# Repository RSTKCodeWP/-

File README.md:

# RSTKCodeWP — FPV & drone open-source library

Монорепозиторій з **каталогом**, **дзеркалами** та **legacy-копіями** FPV/drone проєктів з GitHub.

## Швидка навігація

| Документ | Зміст |
|----------|--------|
| **[wiki/Home.md](wiki/Home.md)** | Виставкова вікі: ідея, для чого, для кого, функція, як, що треба, інструкція |
| **[MAP.md](MAP.md)** | Карта всіх тек монорепо — дерево, org-бібліотеки, статус mirror |
| **[REPOS.md](REPOS.md)** | Повний список усіх проєктів: опис · тека · дата · розмір |
| **[docs/STRUCTURE.md](docs/STRUCTURE.md)** | Структура тек і правила іменування |
| **[fpv-library/](fpv-library/)** | Автокаталог (discover → triage → sync) |
| **[fpv-library/THEMED.md](fpv-library/THEMED.md)** | Тематичні добірки (GCS, WFB, OpenIPC, Caddx…) |
| **[fpv-library/docs/ASCENT.md](fpv-library/docs/ASCENT.md)** | Walksnail / Caddx Ascent — прошивки та RE |
| **[fpv-library/HOOKS.md](fpv-library/HOOKS.md)** | Цікаві / watch репо |

## Структура (коротко)

```
/
├── MAP.md                   # автоген: карта тек + org-бібліотеки
├── REPOS.md                 # автоген: кожен репо + опис + розмір + дата
├── docs/STRUCTURE.md        # що означає кожна тека
├── fpv-library/
│   ├── catalog.json         # маніфест 520+ проєктів
│   ├── repos/               # дзеркала GitHub (auto-sync)
│   ├── scripts/             # discover, sync, triage, Caddx tools
│   ├── manifests/           # SHA256 релізів (firmware, ground config)
│   ├── docs/ASCENT.md       # Ascent firmware + RE index
│   ├── ground-config/       # завантажені Caddx Ground Configuration
│   ├── funnel-queries.txt   # широкий funnel discovery
│   ├── THEMED.md            # кураторський індекс
│   └── HOOKS.md             # hooks / watch list
├── Steer-iOS-RC-Car-FPV/    # legacy: ручні копії з описовою назвою теки
├── SkySweep32-ESP32-Drone-Detector/
└── …
```

**Іменування legacy-тек:** `RepoName-Короткий-Опис` (напр. `wfb-ng-WiFi-FPV-Long-Range-Radio-Link`).

**Іменування sync-тек:** `fpv-library/repos/{repo}-{опис-з-GitHub}/`.

## Команди

```bash
# Оновити повний індекс REPOS.md (опис, дати, розміри)
python3 fpv-library/scripts/generate_repo_index.py

# Пошук + sync
python3 fpv-library/scripts/discover_keywords.py --pages 1 --expand-owners
python3 fpv-library/scripts/sync.py --all --verdict keep --update-only

# Caddx релізи
python3 fpv-library/scripts/sync_caddx_ground_config.py --download
python3 fpv-library/scripts/download_caddx_firmware.py
```

## CI

[`.github/workflows/fpv-library-sync.yml`](.github/workflows/fpv-library-sync.yml) — щодня: discover → triage → sync → оновлення `REPOS.md` → commit.

## Legacy-групи (ручні копії в корені)

Деталі в [REPOS.md § Legacy](REPOS.md#legacy-копії-в-корені).

| Група | Приклади |
|-------|----------|
| FPVibe | `fpv-inventory-…`, `fpv-tools-…`, `flowchart-…` |
| bobberdolle1 (FPV) | `SkySweep32-…`, `GyroChad-…`, `openflash-…` |
| paulnurkkala | Betaflight Claude plugins, `hackrf-vtx-elrs-monitor-…` |
| Приклади | `Steer-iOS-RC-Car-FPV`, `wfb-ng-WiFi-FPV-Long-Range-Radio-Link` |

## Статистика

Див. заголовок [REPOS.md](REPOS.md) — кількість проєктів, сумарний розмір, дата оновлення каталогу.

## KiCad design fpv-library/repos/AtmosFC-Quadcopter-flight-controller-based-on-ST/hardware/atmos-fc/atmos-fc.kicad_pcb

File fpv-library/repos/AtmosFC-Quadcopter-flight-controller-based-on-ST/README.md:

# AtmosFC

AtmosFC is an open-hardware quadcopter flight controller designed in KiCad. Powered by an STM32G4 MCU, it integrates high-performance sensors and peripherals, and is fully compatible with Betaflight (≥ 4.5).

## Table of Contents
- [Features](#features)
- [Input / Output](#input--output)
- [Hardware Architecture](#hardware-architecture)
- [Flashing Betaflight](#flashing-betaflight)
- [Notes](#notes)
- [Gallery](#gallery)
- [Repository Structure](#repository-structure)
- [License](#license)

## Features

- **MCU**: STM32G473CEU6
- **IMU**: ICM-468-P
- **Barometer**: DPS-386
- **OSD**: MAX7456 for analog on-screen display
- **Blackbox**: 32MB onboard flash memory for log recording
- **Power input**: Up to 6S
- **Power monitoring**: Battery voltage and current sensing
- **Status indicators**: Green, Blue, and Amber LEDs
- **Dimensions**: 40x40mm
- **Mounting holes**: 30.5×30.5 mm (M4 holes for silicone inserts with M3 screws)
- **Weight**: 8.2g

## Input / Output 

- **USB connector**: USB Type-C
- **Motor outputs**: x4
- **ESC**: Current sensing and telemetry
- **UARTs**: x3
- **I2C**: Yes
- **Video Input / Video Output with OSD** 
- **5V outputs**: up to 3A total 
- **Buzzer output**

## Hardware Architecture

The block diagram below shows the main hardware components and their interconnections.

##  Flashing Betaflight

AtmosFC runs **Betaflight ≥ 4.5**. You can either flash the precompiled Betaflight 4.5 firmware or build the latest from source.

### Option 1 – Using the provided firmware
1. Open **Betaflight Configurator**.  
   If you don’t have it installed, get the latest version here : [Betaflight Configurator Releases](https://github.com/betaflight/betaflight-configurator/releases/latest)
3. Connect AtmosFC via USB-C.
4. If required, enter DFU mode (hold the BOOT button while plugging in USB).
5. In the Betaflight Configurator, go to **Firmware Flasher → Load firmware [Local]** and select the file `betaflight_4.5.0_ATMOSFC.hex` in `betaflight_config/`.
6. Click **Flash Firmware** and wait for the board to reboot.

### Option 2 – Building from Source

1. Clone the [Betaflight Repository](https://github.com/betaflight/betaflight) and install the required toolchain. Follow the official setup guide for your OS : [Betaflight Building Docs](https://betaflight.com/docs/category/building).
2. In the Betaflight root directory, update the target list by running:
```
> make configs
```
3. Add the AtmosFC board configuration by copying the folder `betaflight_config/ATMOSFC/` into `betaflight/src/config/configs`.
4. Build the firmware for AtmosFC target.
```
> make ATMOSFC
```
5. The compiled `.hex` file will be located under `betaflight/obj/`.
Flash it using **Betaflight Configurator** (follow the steps from Option 1).

## Notes 
- The board has been **successfully tested with Betaflight 4.5**. All basic functions, including motor outputs, sensors, LEDs, were working correctly.
- **I did not test the OSD feature**, as I was flying using digital FPV goggles instead of analog video.
- There is a small **voltage drop on the VBAT measurement** (~0.2-0.3V) due to the Schottky diode used for reverse polarity protection.  
  - This can be compensated either by applying a software offset in Betaflight, or by using an alternative reverse polarity protection method, such as a MOSFET-based circuit

## Gallery

<p align="center">
  
    <br>
  
    <br>
  
    <br>
  
    <br>
  
</p>

## Repository Structure

The repository is organized as follows:

``` bash
├── hardware/             
│   ├── atmos_fc/           # KiCad project files (.kicad_pcb, .sch, etc.)  
│   ├── assembly/           # Fabrication files (Gerber, BOM)
│   └── lib/                # Custom footprints, symbols, 3D models
├── betaflight_config/
│   ├── ATMOSFC/            # Board configuration for Betaflight ≥ 4.5
│   └── betaflight_4.5.0_ATMOSFC.hex    # Precompiled Betaflight 4.5 firmware
├── documentation/          # Schematic (.pdf), images, logo, block diagram
└── README.md
```

##  License

This project is released under the **[MIT License](LICENSE.txt)**.  
You are free to use, modify, and distribute it.

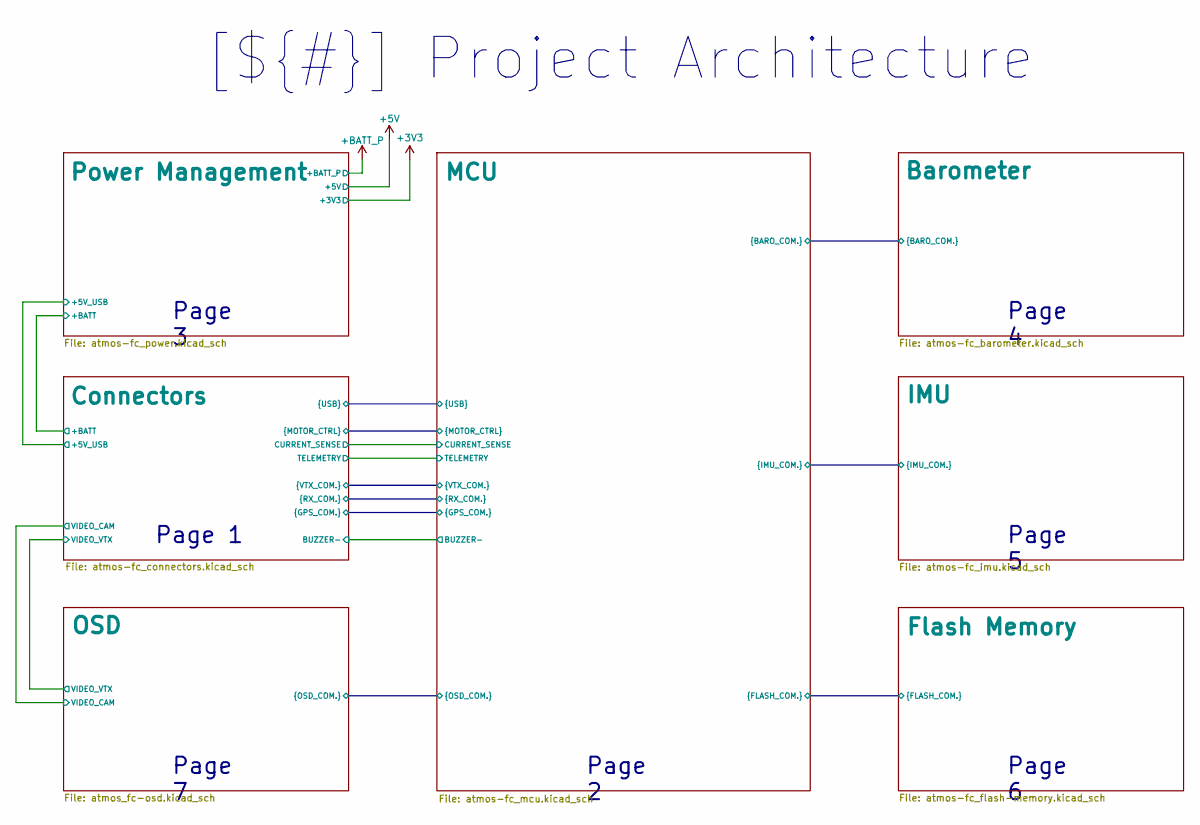
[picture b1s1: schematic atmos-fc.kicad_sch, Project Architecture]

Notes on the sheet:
Page 3
Page 6
Page 4
[${#}] ${TITLE}
Page 5
Page 2
Page 1
Page 7

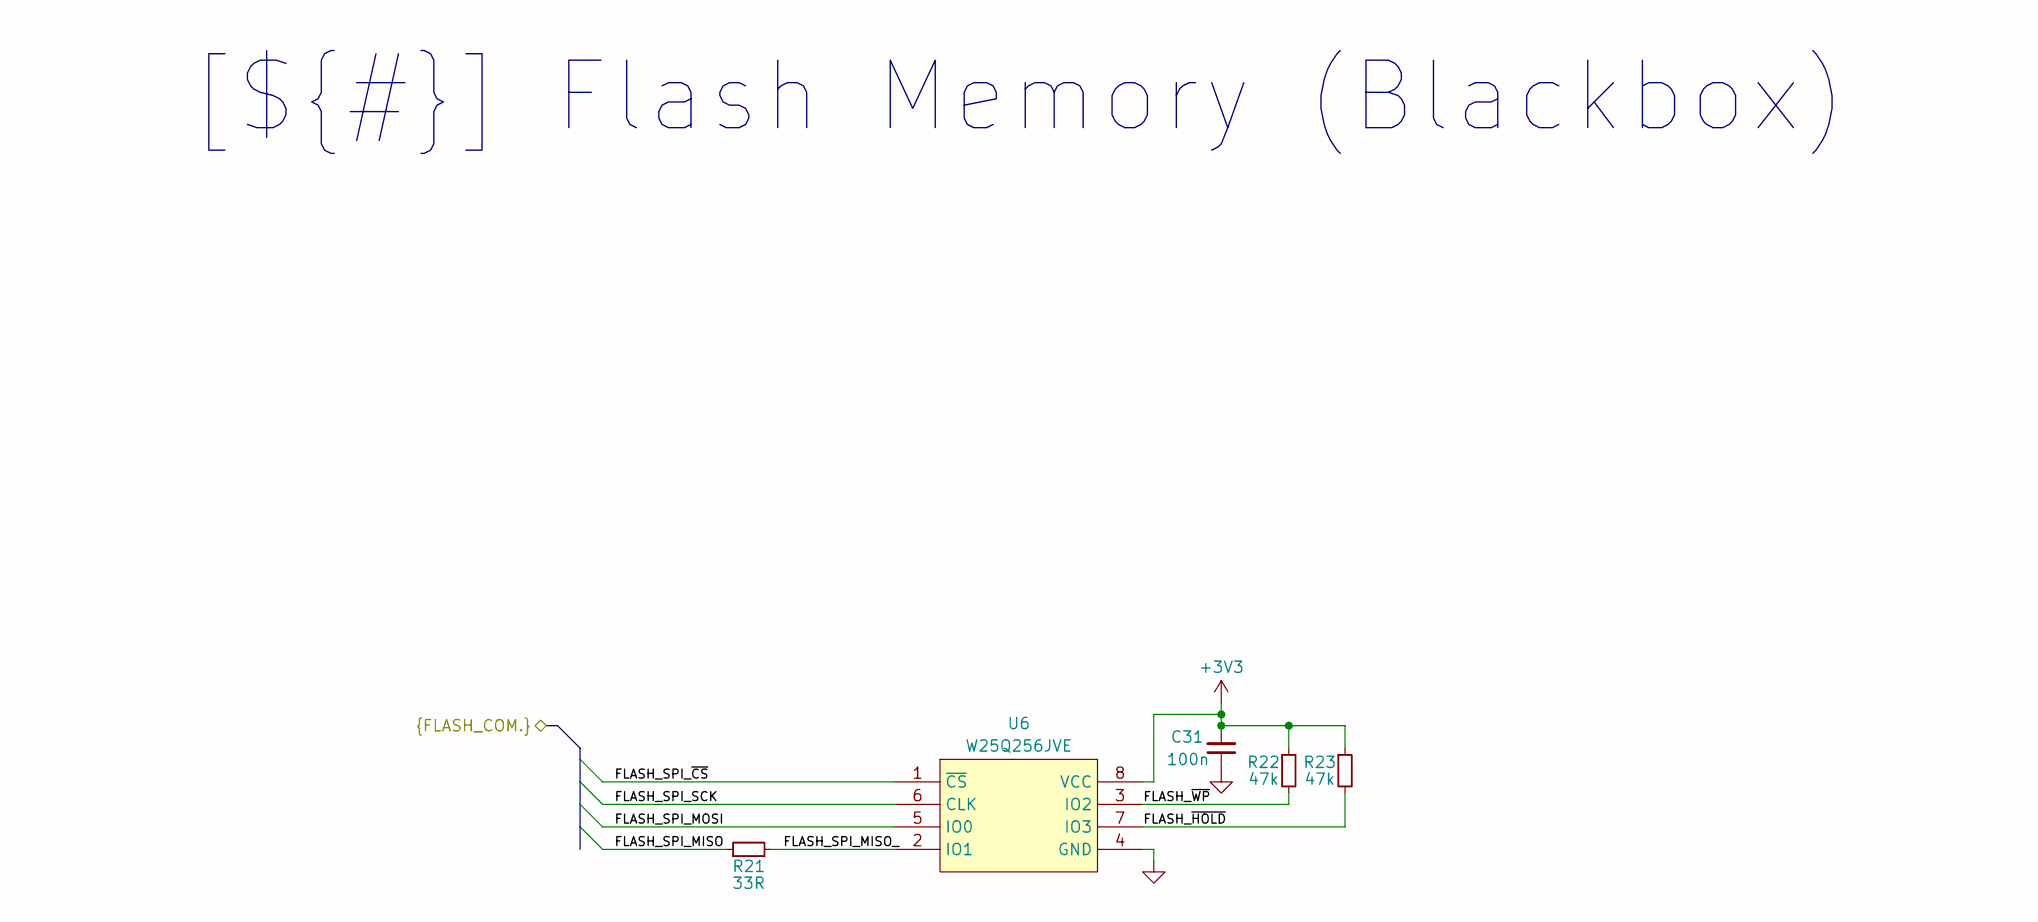
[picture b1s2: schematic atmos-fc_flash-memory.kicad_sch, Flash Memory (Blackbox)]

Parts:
C31: 100n; C_0402_1005Metric; Mfr Part Number MSASE105SB7104KFNA01
R21: 33R; R_0402_1005Metric; Mfr Part Number CRCW040220K0FKED
R22, R23: 47k; R_0402_1005Metric; Mfr Part Number CRCW040247K0FKEDC
U6: W25Q256JVE; WSON-8-1EP_8x6mm_P1.27mm; Mfr Part Number W25Q256JVEIQ

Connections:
+3V3: C31.2, R22.1, R23.1, U6.8 (VCC); also elsewhere on the board
/Flash Memory/FLASH_SPI_MISO: R21.1; also elsewhere on the board
/Flash Memory/FLASH_SPI_MISO_: R21.2, U6.2 (IO1)
/Flash Memory/FLASH_SPI_MOSI: U6.5 (IO0); also elsewhere on the board
/Flash Memory/FLASH_SPI_SCK: U6.6 (CLK); also elsewhere on the board
/Flash Memory/FLASH_SPI_~CS: U6.1 (~CS); also elsewhere on the board
/Flash Memory/FLASH_~HOLD: R23.2, U6.7 (IO3)
/Flash Memory/FLASH_~WP: R22.2, U6.3 (IO2)
GND: C31.1, U6.4 (GND); also elsewhere on the board

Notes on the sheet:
[${#}] ${TITLE}

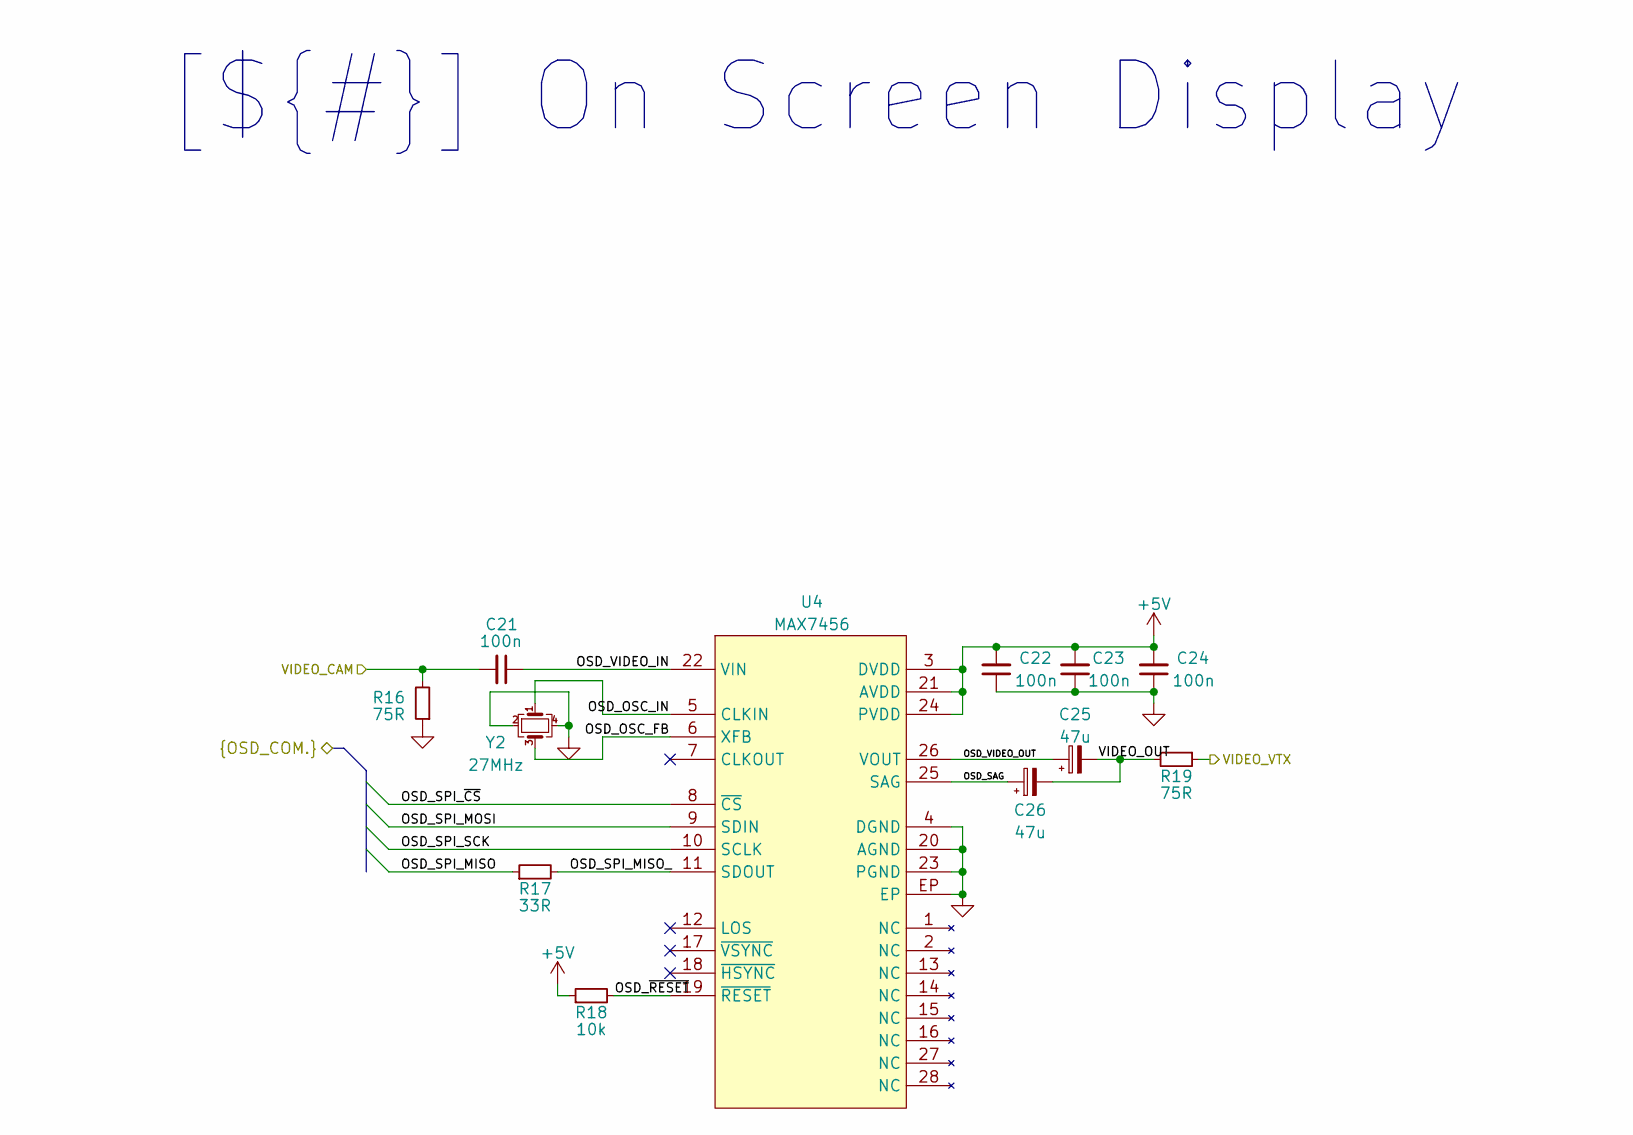
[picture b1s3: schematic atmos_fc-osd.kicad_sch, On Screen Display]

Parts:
C21, C22, C23, C24: 100n; C_0402_1005Metric; Mfr Part Number MSASE105SB7104KFNA01
C25, C26: 47u; CP_EIA-2012-12_Kemet-R; Mfr Part Number F981A476MSAAS1
R16, R19: 75R; R_0402_1005Metric; Mfr Part Number CRCW040275R0FKED
R17: 33R; R_0402_1005Metric; Mfr Part Number CRCW040220K0FKED
R18: 10k; R_0402_1005Metric; Mfr Part Number CRCW040210K0FKEDC
U4: MAX7456; TSSOP-28-1EP_4.4x9.7mm_P0.65mm_EP3.1x6.9mm; Mfr Part Number MAX7456EUI+
Y2: 27MHz; Crystal_SMD_2016-4Pin_2.0x1.6mm; Mfr Part Number CX2016SA27000D0GSSCC

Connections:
+5V: C22.2, C23.2, C24.2, R18.1, U4.3 (DVDD), U4.21 (AVDD), U4.24 (PVDD); also elsewhere on the board
/Connectors/VIDEO_CAM: C21.2, R16.2; also elsewhere on the board
/Connectors/VIDEO_VTX: R19.1; also elsewhere on the board
/MCU/OSD_SPI_MISO: R17.1; also elsewhere on the board
/MCU/OSD_SPI_MOSI: U4.9 (SDIN); also elsewhere on the board
/MCU/OSD_SPI_SCK: U4.10 (SCLK); also elsewhere on the board
/MCU/OSD_SPI_~CS: U4.8 (~CS); also elsewhere on the board
/OSD/OSD_OSC_FB: U4.6 (XFB), Y2.3
/OSD/OSD_OSC_IN: U4.5 (CLKIN), Y2.1
/OSD/OSD_SAG: C26.1, U4.25 (SAG)
/OSD/OSD_SPI_MISO_: R17.2, U4.11 (SDOUT)
/OSD/OSD_VIDEO_IN: C21.1, U4.22 (VIN)
/OSD/OSD_VIDEO_OUT: C25.1, U4.26 (VOUT)
/OSD/OSD_~RESET: R18.2, U4.19 (~RESET)
/OSD/VIDEO_OUT: C25.2, C26.2, R19.2
GND: C22.1, C23.1, C24.1, R16.1, U4.4 (DGND), U4.20 (AGND), U4.23 (PGND), U4.EP, Y2.2, Y2.4; also elsewhere on the board

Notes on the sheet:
[${#}] ${TITLE}

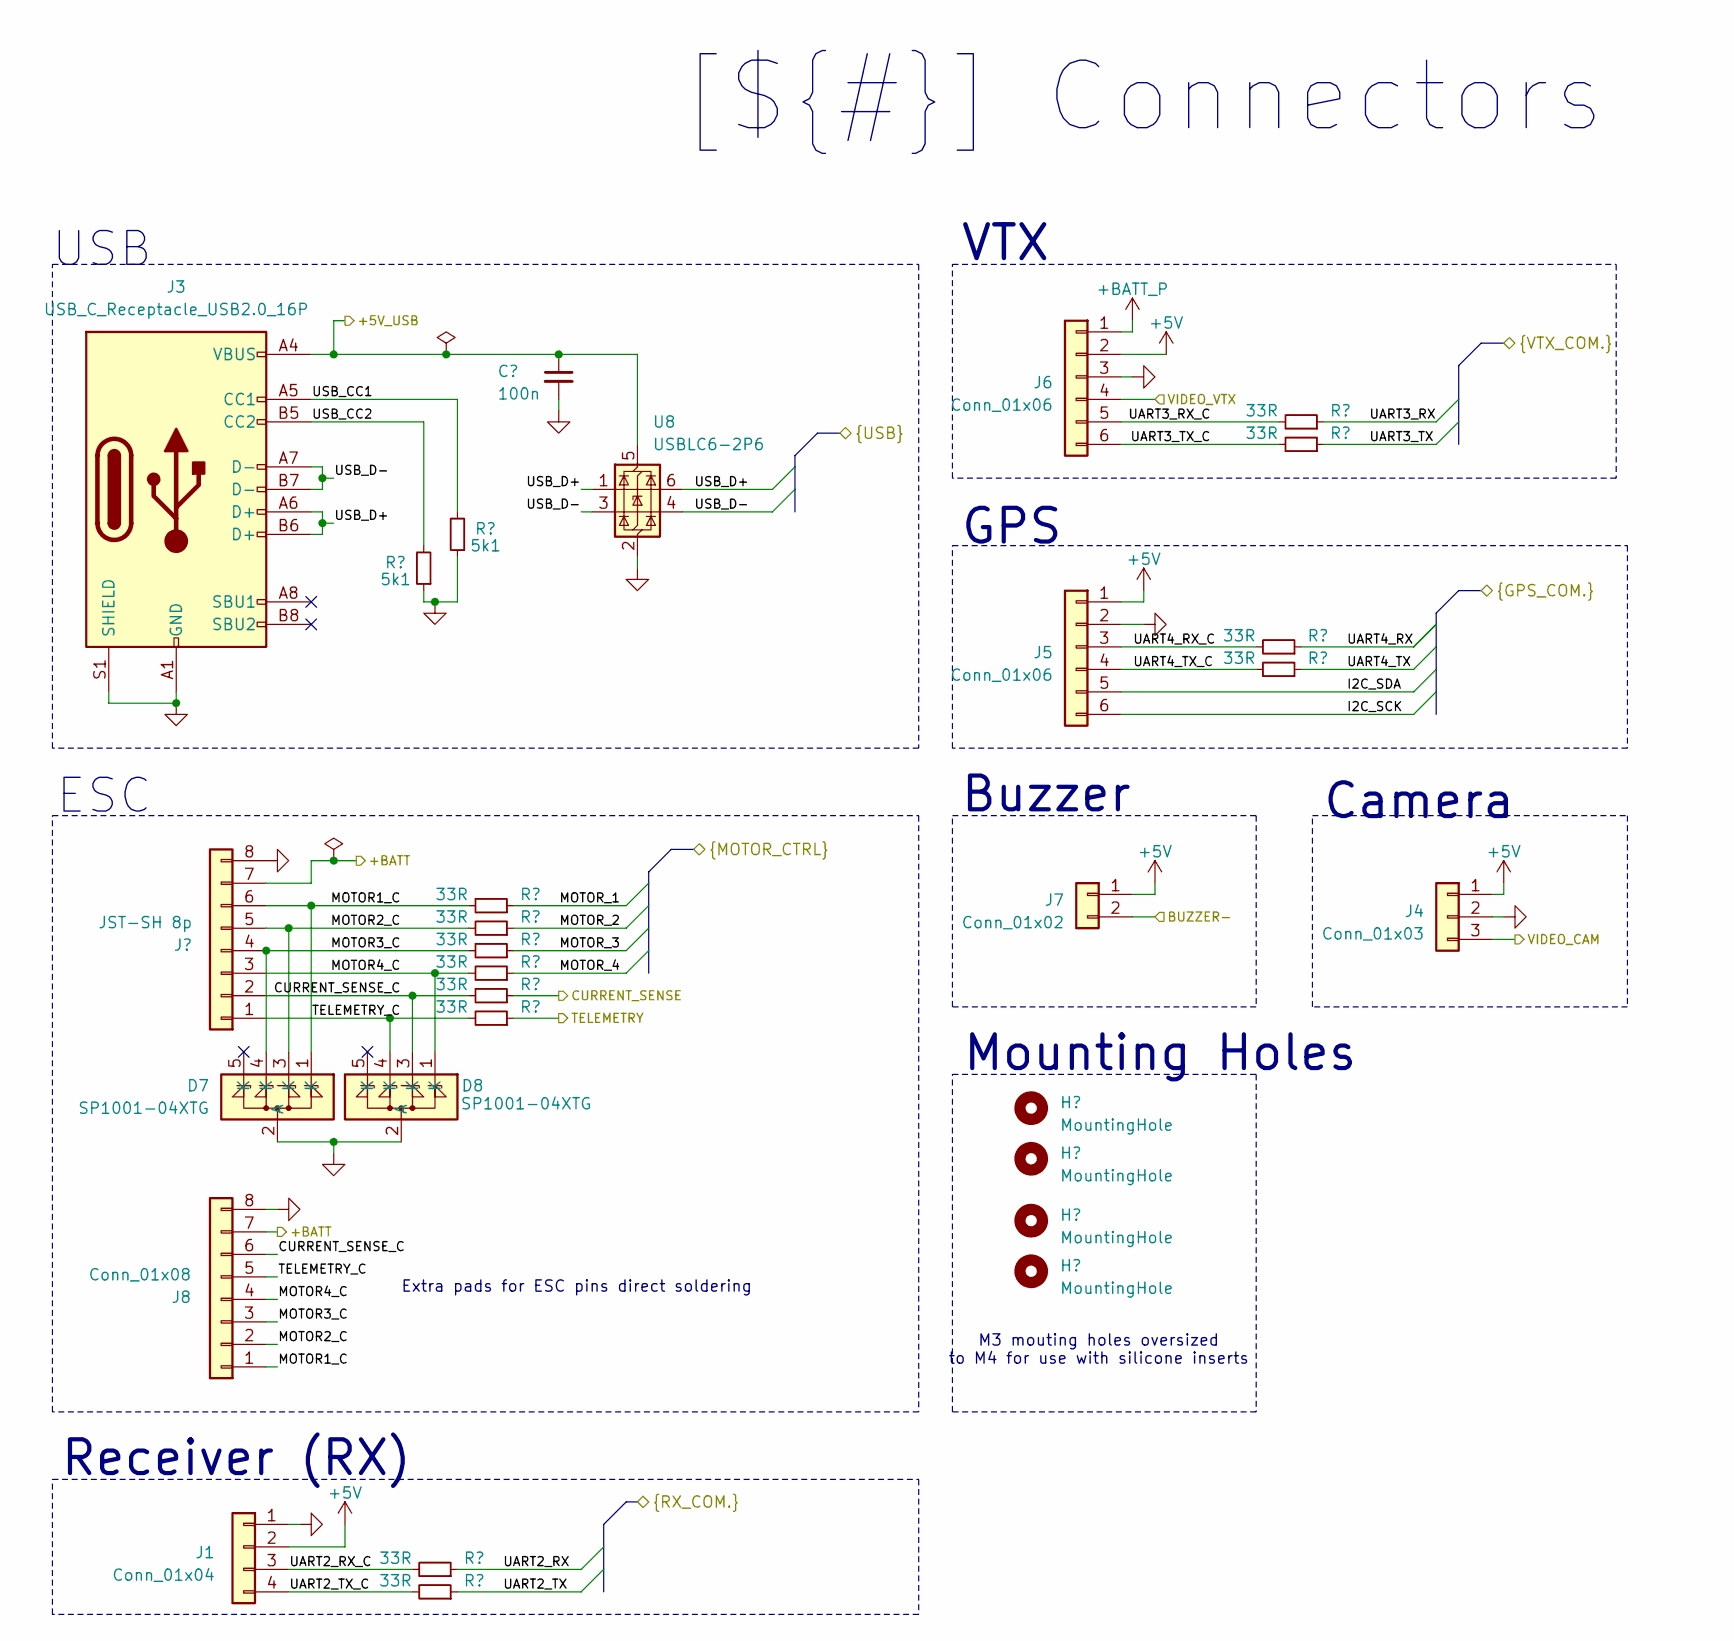
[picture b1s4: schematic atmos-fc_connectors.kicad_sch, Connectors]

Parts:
C34: 100n; C_0402_1005Metric; Mfr Part Number MSASE105SB7104KFNA01
D7, D8: SP1001-04XTG; SOT-553; Mfr Part Number SP1001-04XTG
H1, H2, H3, H4: MountingHole; MountingHole_4.3mm_M4
J1: Conn_01x04; SolderWirePads-2x2
J2: JST-SH 8p; JST_SR_SM08B-SRSS-TB; Mfr Part Number SM08B-SRSS-TB
J3: USB_C_Receptacle_USB2.0_16P; USB_C_Receptacle_GCT_USB4105-xx-A_16P_TopMnt_Horizontal; Mfr Part Number USB4105-GF-A
J4: Conn_01x03; SolderWirePads-1x3
J5, J6: Conn_01x06; SolderWirePads-1x6
J7: Conn_01x02; SolderWirePads-2x1
J8: Conn_01x08; SolderWirePads-2x4
R25, R26: 5k1; R_0402_1005Metric; Mfr Part Number CRCW04025K10FKED
R27, R28, R29, R30, R31, R32, R33, R34, R35, R36, R37, R38: 33R; R_0402_1005Metric; Mfr Part Number CRCW040220K0FKED
U8: USBLC6-2P6; SOT-666; Mfr Part Number USBLC6-2P6

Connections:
+5V: J1.2, J4.1, J5.1, J6.2, J7.1; also elsewhere on the board
+BATT_P: J6.1; also elsewhere on the board
/Connectors/+5V_USB: C34.1, J3.A4 (VBUS), J3.A9 (VBUS), J3.B4 (VBUS), J3.B9 (VBUS), U8.5 (VBUS); also elsewhere on the board
/Connectors/+BATT: J2.7, J8.7; also elsewhere on the board
/Connectors/BUZZER-: J7.2; also elsewhere on the board
/Connectors/CURRENT_SENSE: R31.1; also elsewhere on the board
/Connectors/CURRENT_SENSE_C: D8.3 (K), J2.2, J8.6, R31.2
/Connectors/I2C_SCK: J5.6; also elsewhere on the board
/Connectors/I2C_SDA: J5.5; also elsewhere on the board
/Connectors/MOTOR1_C: D7.1 (K), J2.6, J8.1, R27.2
/Connectors/MOTOR2_C: D7.3 (K), J2.5, J8.2, R28.2
/Connectors/MOTOR3_C: D7.4 (K), J2.4, J8.3, R29.2
/Connectors/MOTOR4_C: D8.1 (K), J2.3, J8.4, R30.2
/Connectors/MOTOR_1: R27.1; also elsewhere on the board
/Connectors/MOTOR_2: R28.1; also elsewhere on the board
/Connectors/MOTOR_3: R29.1; also elsewhere on the board
/Connectors/MOTOR_4: R30.1; also elsewhere on the board
/Connectors/TELEMETRY: R32.1; also elsewhere on the board
/Connectors/TELEMETRY_C: D8.4 (K), J2.1, J8.5, R32.2
/Connectors/UART2_RX: R33.1; also elsewhere on the board
/Connectors/UART2_RX_C: J1.3, R33.2
/Connectors/UART2_TX: R34.1; also elsewhere on the board
/Connectors/UART2_TX_C: J1.4, R34.2
/Connectors/UART3_RX: R37.1; also elsewhere on the board
/Connectors/UART3_RX_C: J6.5, R37.2
/Connectors/UART3_TX: R38.1; also elsewhere on the board
/Connectors/UART3_TX_C: J6.6, R38.2
/Connectors/UART4_RX: R35.1; also elsewhere on the board
/Connectors/UART4_RX_C: J5.3, R35.2
/Connectors/UART4_TX: R36.1; also elsewhere on the board
/Connectors/UART4_TX_C: J5.4, R36.2
/Connectors/USB_CC1: J3.A5 (CC1), R26.2
/Connectors/USB_CC2: J3.B5 (CC2), R25.2
/Connectors/USB_D+: J3.A6 (D+), J3.B6 (D+), U8.1 (I/O1), U8.6 (I/O1); also elsewhere on the board
/Connectors/USB_D-: J3.A7 (D-), J3.B7 (D-), U8.3 (I/O2), U8.4 (I/O2); also elsewhere on the board
/Connectors/VIDEO_CAM: J4.3; also elsewhere on the board
/Connectors/VIDEO_VTX: J6.4; also elsewhere on the board
GND: C34.2, D7.2 (A), D8.2 (A), J1.1, J2.8, J3.A1 (GND), J3.A12 (GND), J3.B1 (GND), J3.B12 (GND), J3.S1 (SHIELD), J4.2, J5.2, J6.3, J8.8, R25.1, R26.1, U8.2 (GND); also elsewhere on the board

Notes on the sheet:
[${#}] ${TITLE}
Camera
M3 mouting holes oversized to M4 for use with silicone inserts
Mounting Holes
Receiver (RX)
ESC
Buzzer
VTX
Extra pads for ESC pins direct soldering
GPS
USB

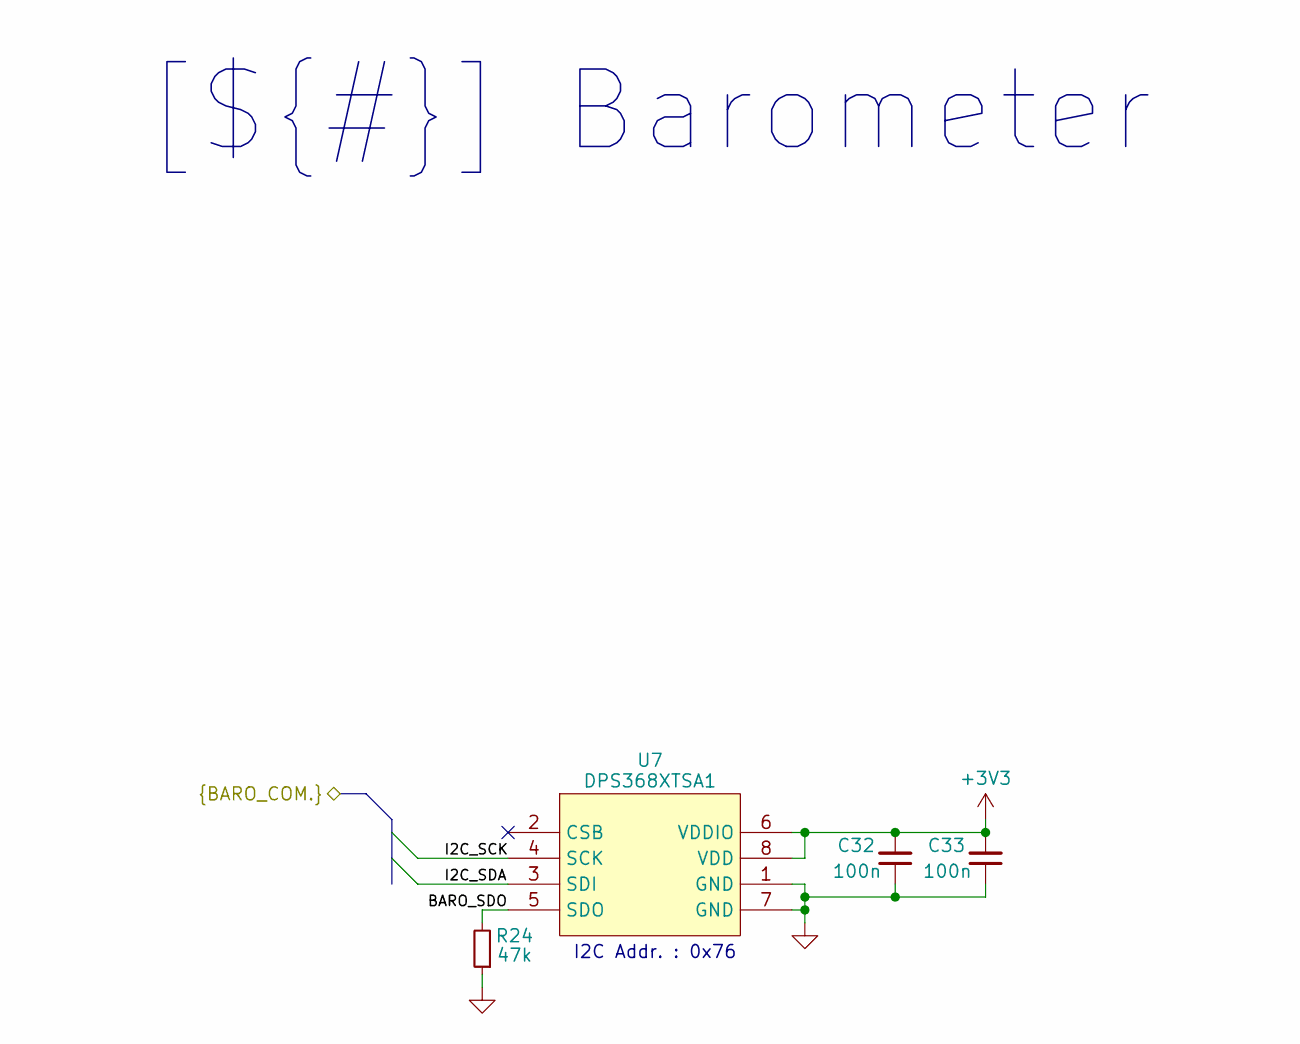
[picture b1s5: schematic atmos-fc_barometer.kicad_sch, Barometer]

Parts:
C32, C33: 100n; C_0402_1005Metric; Mfr Part Number MSASE105SB7104KFNA01
R24: 47k; R_0402_1005Metric; Mfr Part Number CRCW040247K0FKEDC
U7: DPS368XTSA1; Infineon_PG-VLGA-8-2; Mfr Part Number DPS368XTSA1

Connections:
+3V3: C32.2, C33.2, U7.6 (VDDIO), U7.8 (VDD); also elsewhere on the board
/Barometer/BARO_SDO: R24.2, U7.5 (SDO)
/Connectors/I2C_SCK: U7.4 (SCK); also elsewhere on the board
/Connectors/I2C_SDA: U7.3 (SDI); also elsewhere on the board
GND: C32.1, C33.1, R24.1, U7.1 (GND), U7.7 (GND); also elsewhere on the board

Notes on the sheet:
[${#}] ${TITLE}
I2C Addr. : 0x76

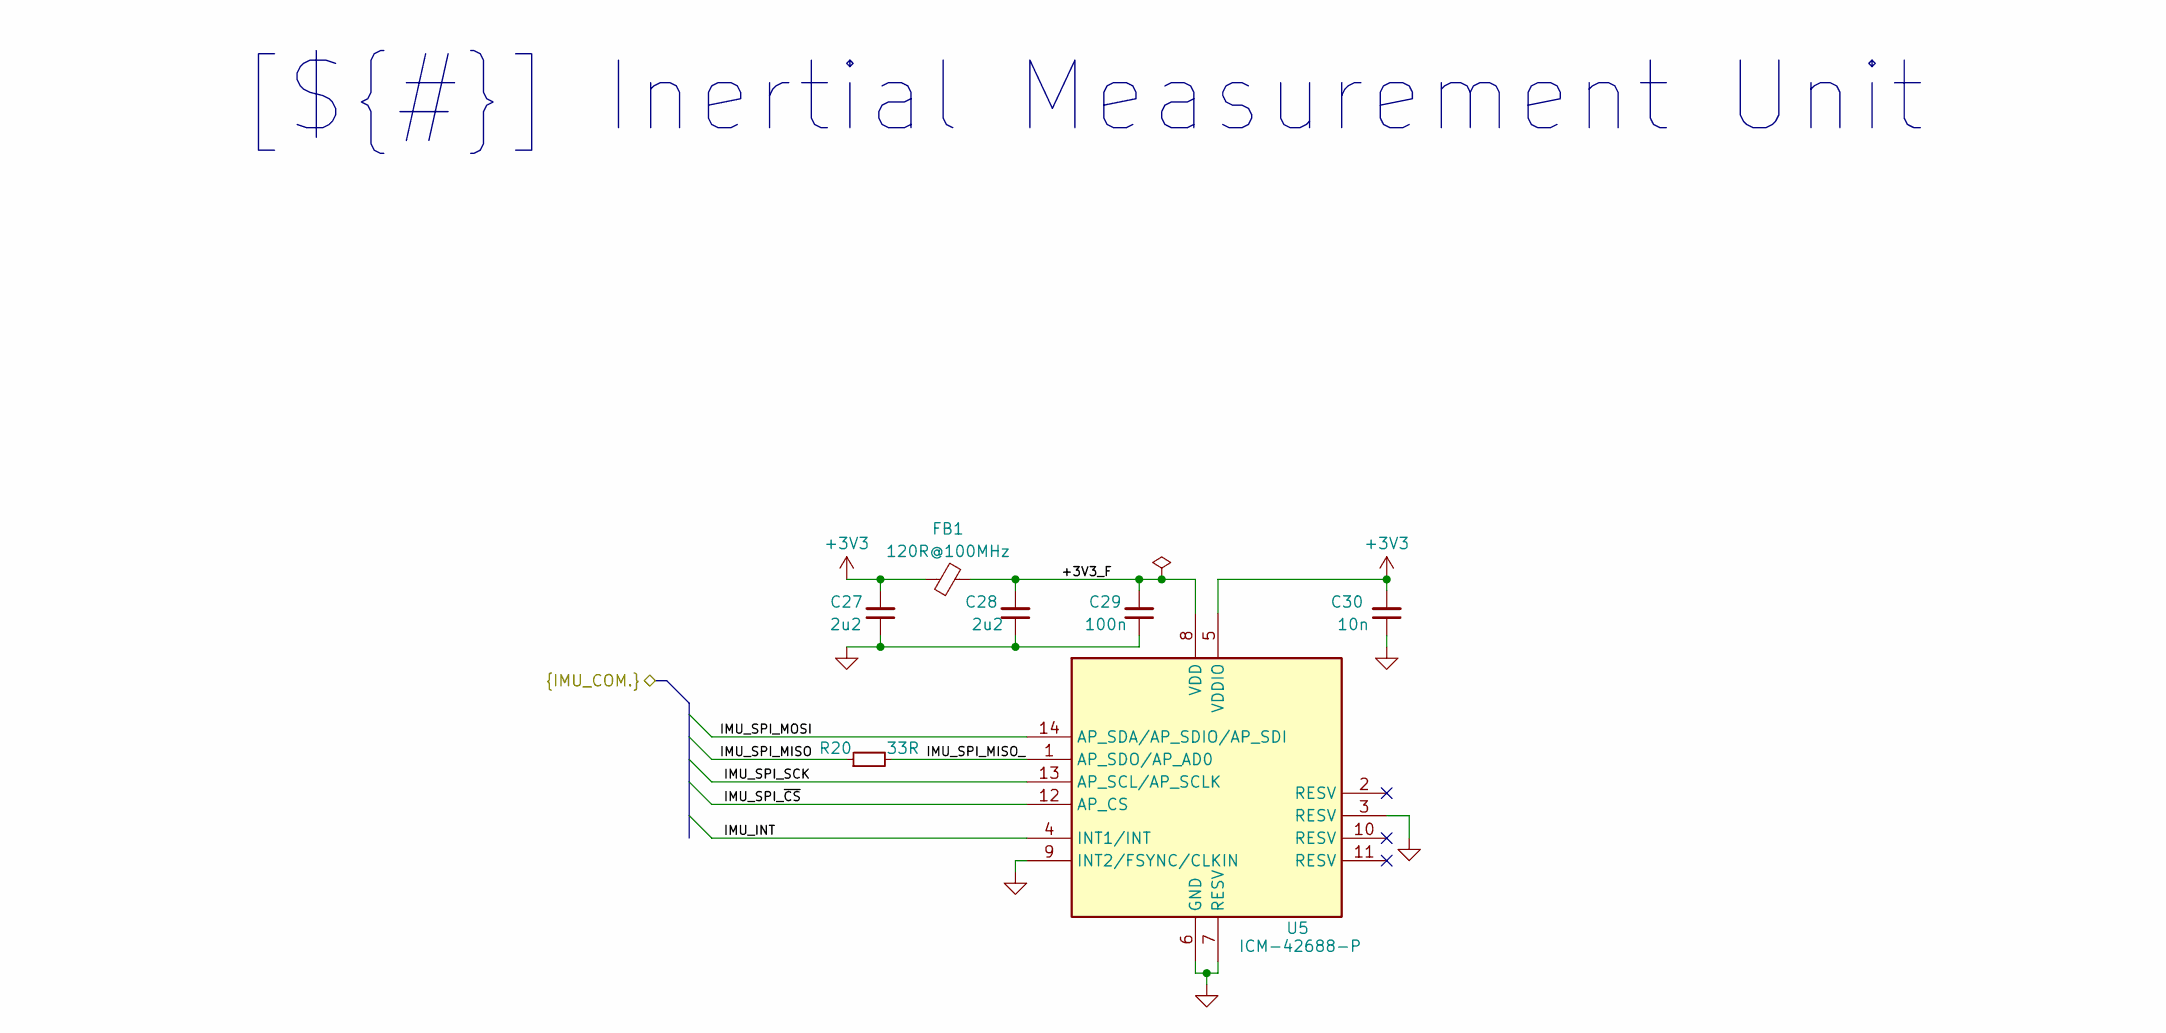
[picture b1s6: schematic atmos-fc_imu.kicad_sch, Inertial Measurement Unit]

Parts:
C27, C28: 2u2; C_0402_1005Metric; Mfr Part Number GRM155C71A225KE11D
C29: 100n; C_0402_1005Metric; Mfr Part Number MSASE105SB7104KFNA01
C30: 10n; C_0402_1005Metric; Mfr Part Number GRM1555C1E103GE01D
FB1: 120R@100MHz; L_0402_1005Metric; Mfr Part Number BLM15PX121BH1D
R20: 33R; R_0402_1005Metric; Mfr Part Number CRCW040220K0FKED
U5: ICM-42688-P; Mfr Part Number ICM-42688-P

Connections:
+3V3: C27.2, C30.2, FB1.1, U5.5 (VDDIO); also elsewhere on the board
/IMU/+3V3_F: C28.2, C29.2, FB1.2, U5.8 (VDD)
/IMU/IMU_INT: U5.4 (INT1/INT); also elsewhere on the board
/IMU/IMU_SPI_MISO: R20.1; also elsewhere on the board
/IMU/IMU_SPI_MISO_: R20.2, U5.1 (AP_SDO/AP_AD0)
/IMU/IMU_SPI_MOSI: U5.14 (AP_SDA/AP_SDIO/AP_SDI); also elsewhere on the board
/IMU/IMU_SPI_SCK: U5.13 (AP_SCL/AP_SCLK); also elsewhere on the board
/IMU/IMU_SPI_~CS: U5.12 (AP_CS); also elsewhere on the board
GND: C27.1, C28.1, C29.1, C30.1, U5.3 (RESV), U5.6 (GND), U5.7 (RESV), U5.9 (INT2/FSYNC/CLKIN); also elsewhere on the board

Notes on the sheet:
[${#}] ${TITLE}

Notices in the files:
SkySweep32-ESP32-Drone-Detector/README.md:
License: GPL v3
SkySweep32-ESP32-Drone-Detector/hardware/skysweep32_pro.kicad_pcb:
v1.0  2026-07-16  GPL-3.0
